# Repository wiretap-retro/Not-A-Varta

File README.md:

# Not-A-Varta
A standard 19mm length Varta replacement with a CR1220 and charge protection.

## Info
This is a battery replacement for old circuit boards utilizing the 19mm length 3.6V Varta battery. The replacement is a 3V CR1220 with charge circuit protection. Low voltage drop is achieved with the MAX40200 "ideal diode" chip. Most boards will work with RTC/CMOS function at 3V, so check datasheets before you go through the hassle of building and installing this. Some motherboards have additional diodes that need to be bypassed. Clean up any corrosion from the pre-existing evil Varta before installation.
\
\
CR2032 version here: https://github.com/wiretap-retro/Not-A-Varta-CR2032
\
\
Open hardware design. Do what you want with it.

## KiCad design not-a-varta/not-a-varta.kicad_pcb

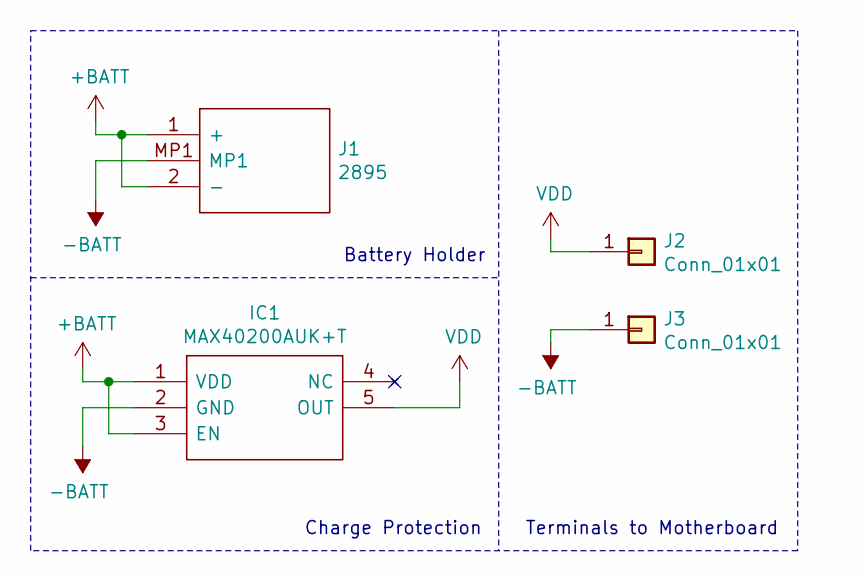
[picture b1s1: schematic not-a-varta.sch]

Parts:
IC1: MAX40200AUK+T; SOT95P280X145-5N; Mouser Part Number 700-MAX40200AUK+T
J1: 2895; Mouser Part Number 534-2895
J2, J3: Conn_01x01; PinHeader_1x01_P2.54mm_Vertical

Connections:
+BATT: IC1.1 (VDD), IC1.3 (EN), J1.1 (+), J1.2 (-)
-BATT: IC1.2 (GND), J1.MP1, J3.1
VDD: IC1.5 (OUT), J2.1

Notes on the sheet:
Charge Protection
Battery Holder
Terminals to Motherboard

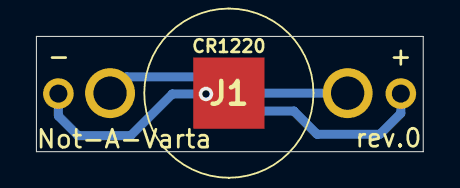
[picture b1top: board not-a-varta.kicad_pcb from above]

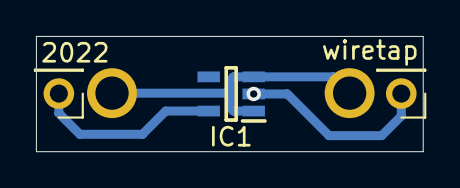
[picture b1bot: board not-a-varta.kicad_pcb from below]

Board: 2 copper layers, 21.5 x 6.4 mm, 4 parts (3 on the bottom side), 3 nets.

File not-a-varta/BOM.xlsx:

Reference | Value | Footprint | Description | Manufacturer_Name | Manufacturer_Part_Number
J1 | 2895 | 2895 | Coin Cell Battery Holders CR1220 COIN CELL THM RETAINER | Keystone Electronics | 2895
IC1 | MAX40200AUK+T | SOT95P280X145-5N | OR Controller Source Selector Switch P-Channel 1:1 SOT-23-5 | Maxim Integrated | MAX40200AUK+T
J2, J3 | Conn_01x01 | Connector_PinHeader_2.54mm:PinHeader_1x01_P2.54mm_Vertical
